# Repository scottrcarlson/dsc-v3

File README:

Dirt Simple Comms
 
-- Add the content here --

What Packages to Install, Hardware, Configuration etc..

See also: https://bitbucket.org/dsc2/dsc2/wiki

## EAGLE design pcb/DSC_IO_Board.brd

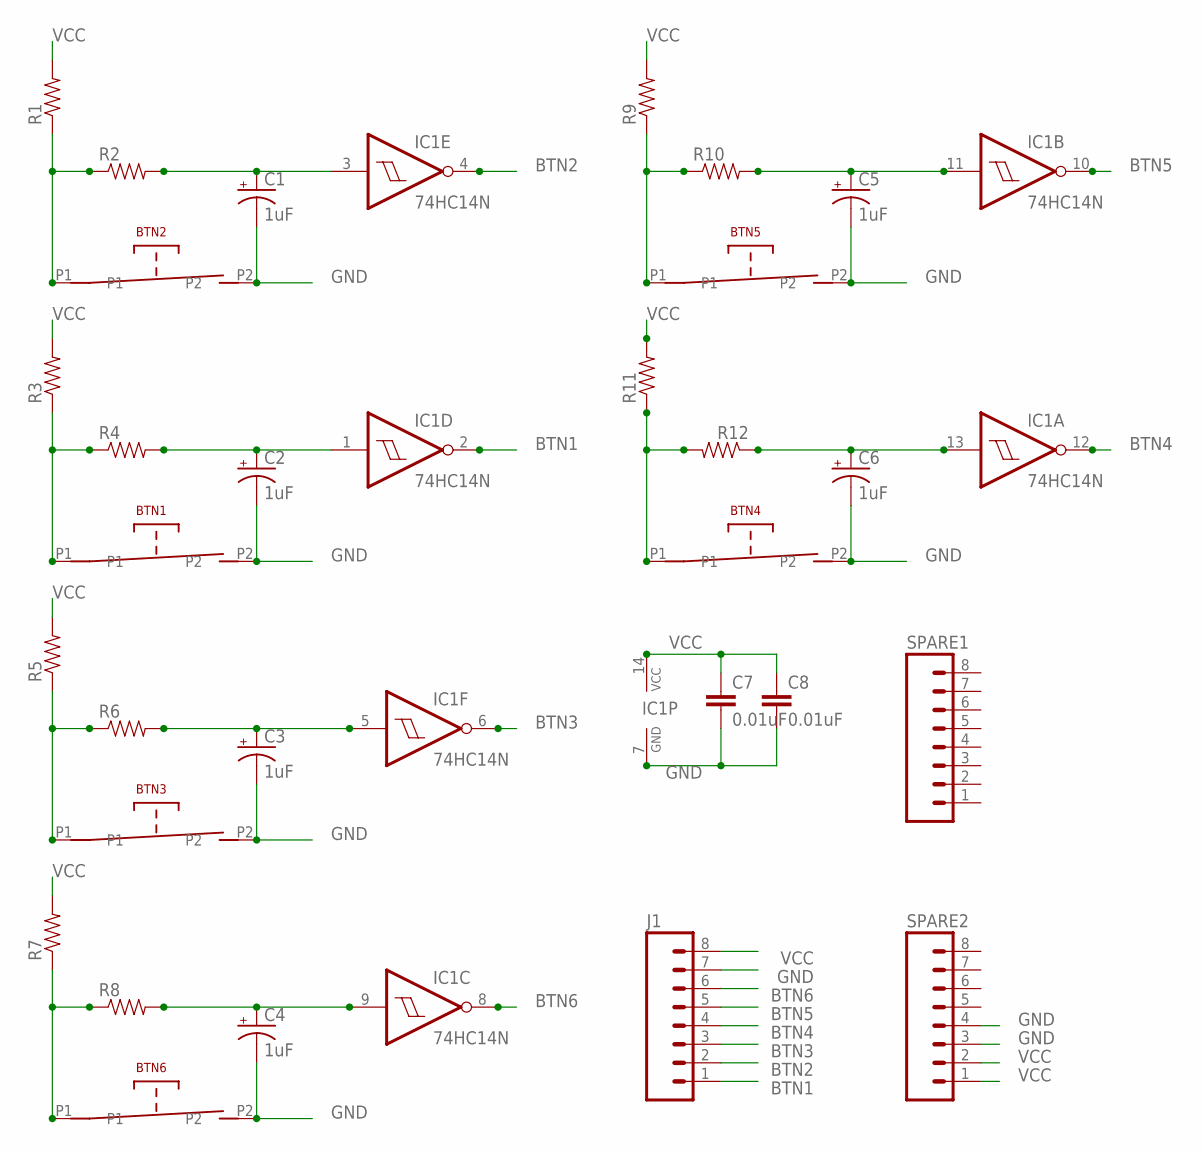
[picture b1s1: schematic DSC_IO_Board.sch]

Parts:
BTN1, BTN2, BTN3, BTN4, BTN5, BTN6: MOMENTARY-TACTILE-SWTICH; MOMENTARY-TACTILE-SWITCH
C1, C2, C3, C4, C5, C6: 1uF; CPOL-RADIAL-10UF-25V-KIT
C7, C8: 0.01uF; CAP-PTH-SMALL
IC1: 74HC14N; DIL14
J1: M08; 1X08_ROUND
R1, R2, R3, R4, R5, R6, R7, R8, R9, R10, R11, R12: 1KOHM-1/4W-1%(PTH); AXIAL-0.3
SPARE1, SPARE2: M08; 1X08_ROUND

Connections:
BTN1: IC1.2 (O), J1.1
BTN2: IC1.4 (O), J1.2
BTN3: IC1.6 (O), J1.3
BTN4: IC1.12 (O), J1.4
BTN5: IC1.10 (O), J1.5
BTN6: IC1.8 (O), J1.6
GND: BTN1.P2, BTN2.P2, BTN3.P2, BTN4.P2, BTN5.P2, BTN6.P2, C1.2 (-), C2.2 (-), C3.2 (-), C4.2 (-), C5.2 (-), C6.2 (-), C7.2, C8.2, IC1.7 (GND), J1.7, SPARE2.3, SPARE2.4
unnamed: BTN4.P1, R11.P$1 (1), R12.P$2 (2)
unnamed: BTN1.P1, R3.P$1 (1), R4.P$1 (1)
unnamed: BTN2.P1, R1.P$1 (1), R2.P$1 (1)
unnamed: C1.1 (+), IC1.3 (I), R2.P$2 (2)
unnamed: C2.1 (+), IC1.1 (I), R4.P$2 (2)
unnamed: BTN3.P1, R5.P$1 (1), R6.P$1 (1)
unnamed: C3.1 (+), IC1.5 (I), R6.P$2 (2)
unnamed: BTN6.P1, R7.P$1 (1), R8.P$1 (1)
unnamed: C4.1 (+), IC1.9 (I), R8.P$2 (2)
unnamed: BTN5.P1, R9.P$1 (1), R10.P$1 (1)
unnamed: C5.1 (+), IC1.11 (I), R10.P$2 (2)
unnamed: C6.1 (+), IC1.13 (I), R12.P$1 (1)
VCC: C7.1, C8.1, IC1.14 (VCC), J1.8, R1.P$2 (2), R3.P$2 (2), R5.P$2 (2), R7.P$2 (2), R9.P$2 (2), R11.P$2 (2), SPARE2.1, SPARE2.2

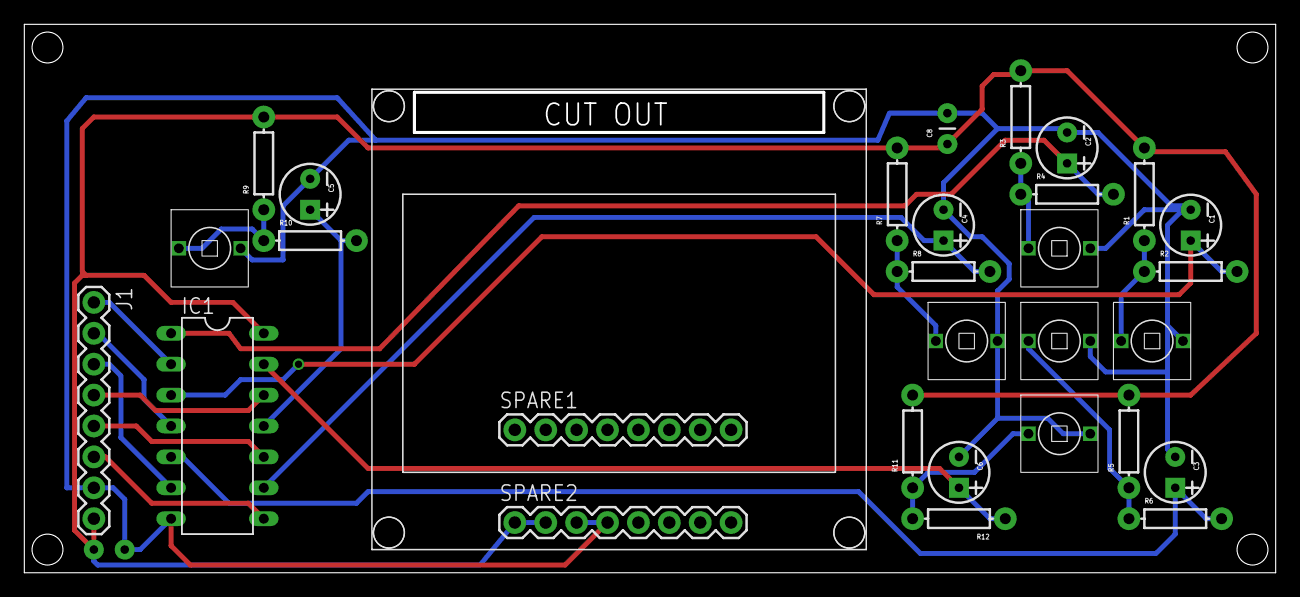
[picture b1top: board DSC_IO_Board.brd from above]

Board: 2 copper layers, 102.6 x 44.8 mm, 31 parts (1 on the bottom side), 20 nets.

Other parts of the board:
U$1: OLED-DISPLAY

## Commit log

2017-07-14 replace assymetric crypto (keyczar module) w/ symmetric (cryptography module)
2017-07-15 New protocol/crypto implementation functional.
2017-07-15 New protocol/crypto scheme almost fully integrated.
2017-07-15 Fixed last few bugs from code overhaul, new msg protocol/crypto fully functional
2017-07-19 init repo. first commit
2017-07-19 Message viewing implemented.
2017-07-21 Messaging bugs, corrected msg list bug, cleaned up some dead wood
2017-07-21 Calculate tx_throttle (delay before next tx) based on packet size
2017-07-21 Cleaning up, removing deadwood
2017-07-22 Cleanup
2017-07-22 Initial Node Registration UI complete. TDMA Settings menu complete
2017-08-01 Commiting changes from Defcon bug crushing sessions.
2017-08-02 Logging exceptions.
2017-08-02 Cleaning up deadwood.
2017-08-02 Added Lock screen. UI Bug fixes.
2017-08-02 Moving files around.
2017-08-02 Implemented horizontal scrolling for large messages. Adding documentation.
2017-08-02 Implemented word wrapping for message composition.
2017-08-02 Added Airplane Mode. Fixed/Smoothed some UI Issues.
2017-08-03 Implemented Radio RF Tuning Param UI Interface. Loads/Save Params to Radio's MCU. Freq/Bandwidth/SpreadFactor/CodingRate/TxPower/SyncWord
2017-08-04 House keeping.
2017-08-04 Bill of Materials (First Pass)
2017-08-06 Fixing up GPS reporting.
2017-08-07 House keeping, removed old v2 hardware design files
2017-08-07 Update README.md
    Updating BOM
2017-08-07 Hotplug GPS / Exposing Stats / Log when fixed.
2018-04-07 Removed static IV
2018-04-07 Improved gps device handling.
2018-04-07 DSCv3 wiring list/lengths
2018-04-07 DSCv3 io definition
2018-04-07 Added motor vibration on msg receipt. cleaned up logging.
2018-04-07 Added RX/TX/Beacon LED indication
2018-04-07 Stubbed Low Battery Handler.
2018-04-07 push
2018-04-07 bare bone log parsing
2018-07-27 Carving out support for DSCv4 (BLE Outboarding Mode) There is an accompanying Android application. Bringing in BLE/GATT Services Re-arrange / Modifications to support DSCv3 and DSCv4 modes.
    BLE Gatt Settings Service fully functional. Persist to Radio/Disk. Syncronize from Android device.
    BLE Gatt Datetime Sync Service. The new units do not have an RTC, we rely on handset to push/sync date and time.
2018-08-08 Detaching system configuration from original display/ui, to support handset via ble
2018-09-01 More refactoring to support standalone/ble outboarding.
    Added back I/O Capabilities for the ble pairing script.
    Implemented Gatt Characteristics:
    Status Notification (When enabled, provides periodic status update. System time, RF state, more things to be added)
    Outbound Messages (A write only characteristic to send messages from handset to the dsc network)
2018-09-01 fixed tdma frame calculations that were only done at startup, now will re-calculate when a network parameter has changed.
    Testing units shows perfect tdma schedules now.
2018-09-02 Re-working the inbound message process. Queue up Beacons for BLE notification to handset.
2018-09-02 Implemented center frequency hopping sequence. This sequence will be called a "virtual channel"
    The sequence takes the secret+epoch to seed the PRNG.
    That seed will be used once per tdma frame start to generate the center frequency to use.
2018-09-02 BLE Gatt Characteristic handles beacon queue.
2018-09-02 General cleanup. Proper padding.
2018-09-21 Intermediate commit.
    Heavy changes in message/radio implementation to support multi-mode protocol.
    The main virtual channel will be dedicated to small rapid exchanges. When a
    node receives the beacon of another, and can infer that there is information to
    be shared, that node will send a special beacon to request a 1 on 1 conversation
    that takes place in a "private virtual channel".
    While 2 nodes are sharing a conversation in the PVC, other nodes may also
2018-09-22 Main/Private virtual channel mechanism is functional.
    The private mode conversation is still utilizing TDMA scheme for 2 nodes.
2018-09-23 Remove Radio Interrupt Channel. This has caused so many ansyncronous related issues. Reading and writing to the radio modules's serial channel is now don syncronously.
    Transmission rate is limited by tx_throttle but can be removed once more computationally expense operations are optimized in adjacent message thread.
    Continuing to add in virtual channel support with individual p2p channels for rapid exchange of information.
2018-09-23 Almost finished with virtual channel support.
    We now calculate theoretical bitrate based on rf parameters. Also implemented a crude signal quality calculation.
    Future Work: Utilize signal quality feedback to dynamically tune rf parameters when entering p2p exchange.
2018-09-23 Clearing outbound radio queue in a better place.
    Cleanup.
2018-09-25 Batching Acknowledgment messages. Linting.
    Prototyping chacha20/poly1305, to replace AES.
    Including small ncurses based chat mockup from Tyler. This would be really cool
    to use in serial gadget mode on the pi.
2018-09-30 Cleanup, proper padding, handle unicode better.
2018-10-03 Fixes and optimization to the protocol.
2018-10-20 House keeping
    prepping to replace aes
2018-10-21 Replaced AES with ChaCha20 Poly1305 AEAD mode.

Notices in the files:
parts and their libraries:
SparkFun-Resistors: Licensing: Creative Commons ShareAlike 4.0 International - https://creativecommons.org/licenses/by-sa/4.0
